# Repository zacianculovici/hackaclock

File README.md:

# hackaclock
My Stardance BLARE alarm clock!!!

## Inspiration
Really, I just saw the BLARE mission and thought it was really cool, but I made the case inspired by one of those old alarm clocks with the angled screens. I also added a cool cutout and some bevelling to make it look nice. 

## Challenges
I ran into some pretty tough issues while doing CAD. I made a dumb decision at the start to use blender for my CAD even though it's not exactly a CAD program. Loads of non-manifold errors and geometry issues (that might just be why my commit history looks terrible). I spent over 13 hours just getting the CAD done! Despite these problems, I am still very happy with the result and the CAD (in my humble opinion) looks great.

## Files
* [Firmware: hackaclock.ino](firmware/hackaclock.ino)
* [Box: Hackaclock-Box.stl](Production/Hackaclock-Box.stl)
* [Lid: Hackaclock-Lid.stl](Production/Hackaclock-Lid.stl)
* [PCB: Board.step](Production/Board.step)
* [Gerbers: fab_files.zip](Production/fab_files.zip)

## Specs
### BOM
* 6x Cherry MX Switches
* 6x Blank Keycaps
* 1x Unimportant jumper header
* 1x XIAO ESP32-C3
* 4x M3x16 bolts
* 4x M3 heat-set inserts
* 1x Buzzer

### Firmware
I am using the most barebones firmware to begin, but I will make it super cool after I build. Currently it only gets the local time via WiFi with no fallback, but I will eventually add:
#### Coming soon
* Alarms
* Manual time setting
* Timer/stopwatch
* Alarm snooze
* Buzzer goes beeeeeeep
* More features...

### CAD
The CAD is a very simple (13h worth of simple) box and lid with a slot for the display and supports for the PCB.

## PCB:
Here is the Schematic and PCB layout for hackaclock.

---
<sup><sub>2026 - Zac Ianculovici | [Contact](mailto:zachary.ianculovici@gmail.com) | [Slack](https://hackclub.enterprise.slack.com/team/U0BMLT1CFB3) | [Stardance](https://stardance.hackclub.com/@zac_i)</sub></sup>

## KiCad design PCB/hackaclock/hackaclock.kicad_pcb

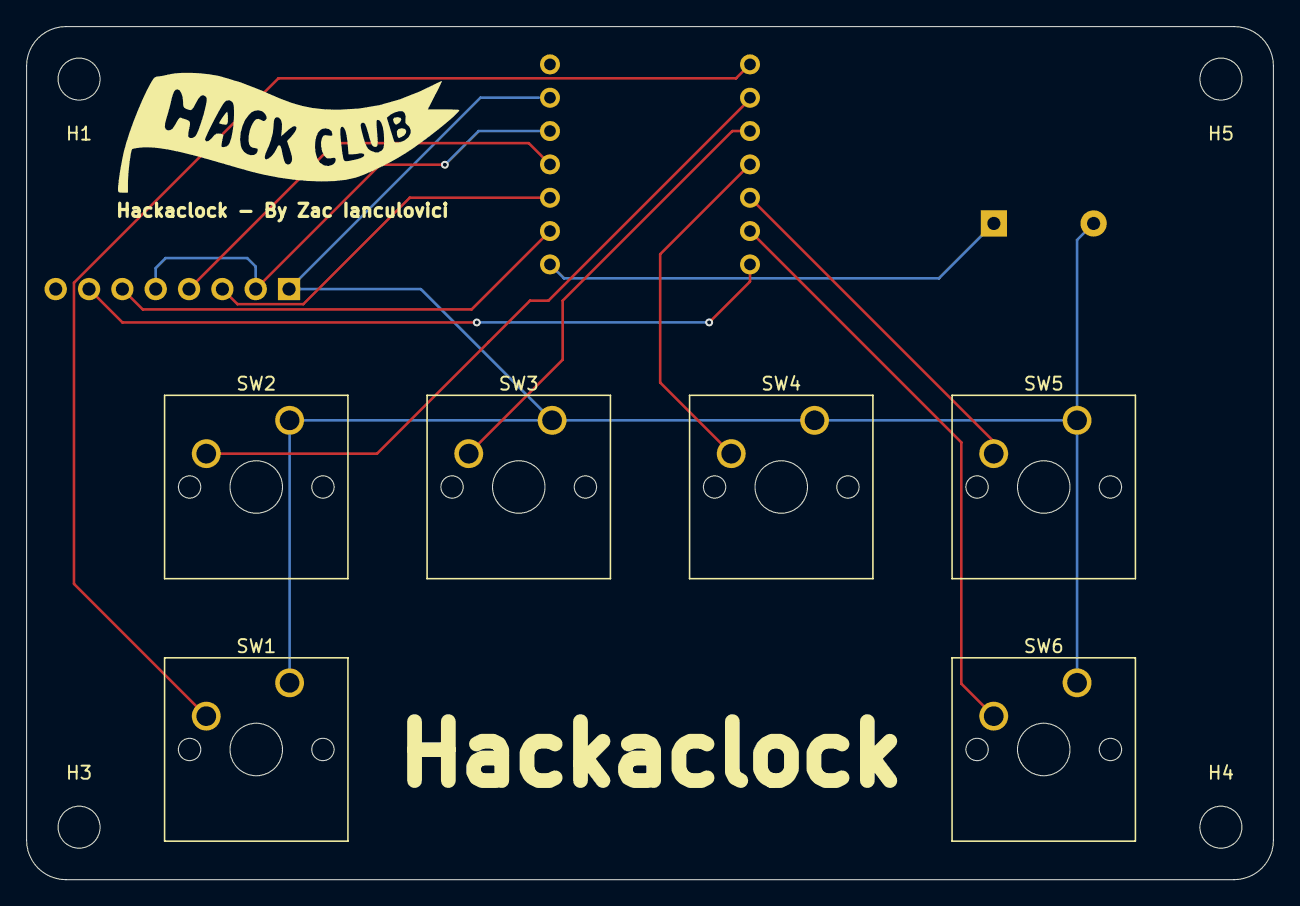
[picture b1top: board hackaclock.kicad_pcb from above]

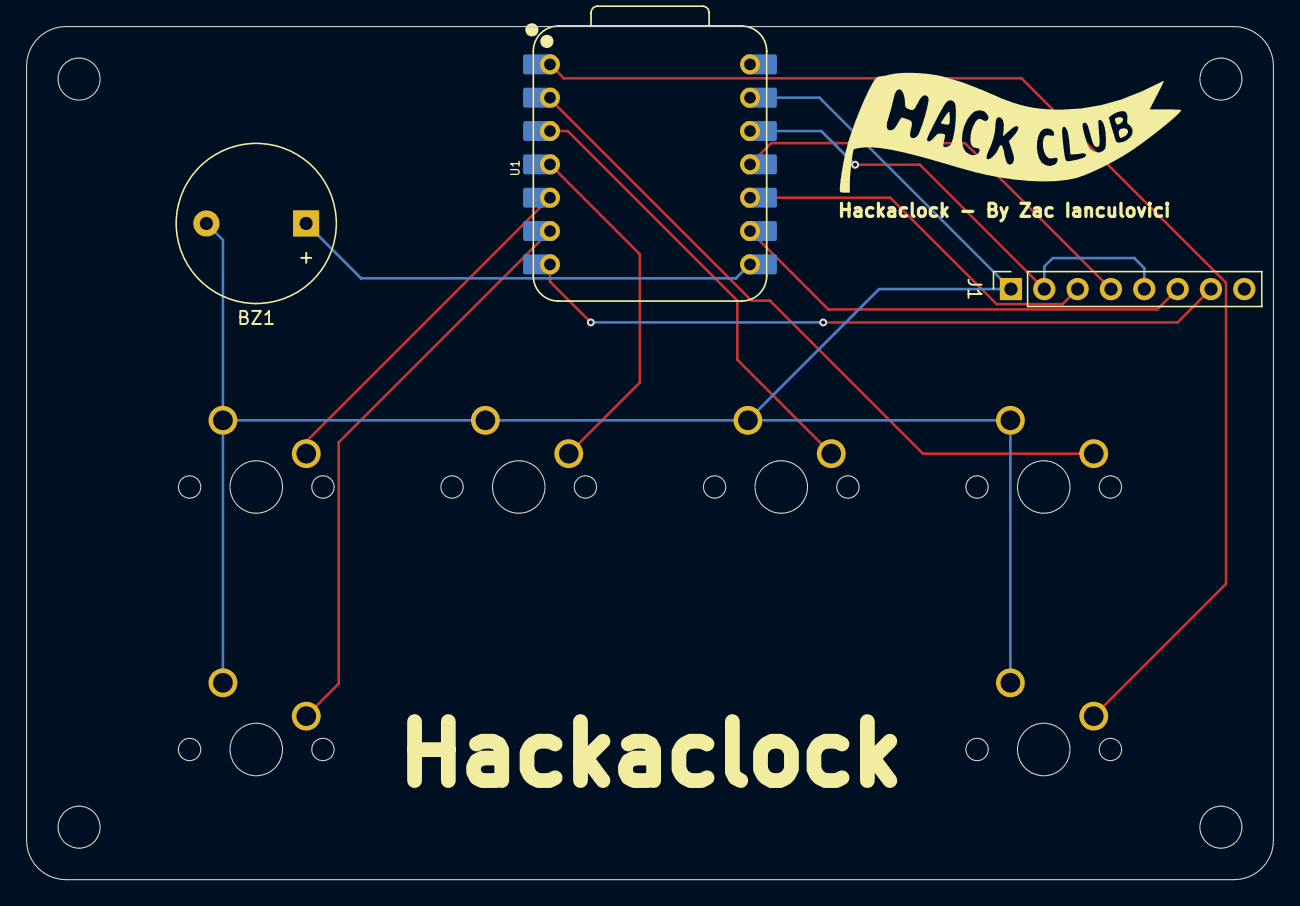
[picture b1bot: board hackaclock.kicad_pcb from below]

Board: 2 copper layers, 95.0 x 65.0 mm, 15 parts (4 on the bottom side), 13 nets.

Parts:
BZ1: Buzzer; Buzzer_12x9.5RM7.6
H1, H3, H4, H5: MountingHole; MountingHole_3.2mm_M3
Hackaclock - By Zac Ianculovici: LOGO
Hackaclock - By Zac Ianculovici#2: LOGO
J1: Conn_01x08_Pin; PinSocket_1x08_P2.54mm_Vertical
SW1, SW2, SW3, SW4, SW5, SW6: SW_Push; SW_Cherry_MX_1.00u_PCB
U1: XIAO-ESP32-C3-SMD; XIAO-ESP32-C3-DIP

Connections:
+3V3: J1.2, J1.5, U1.12 (3V3_OUT)
/CS: J1.7, U1.7 (D6)
/DC: J1.6, U1.9 (D8)
/SCL: J1.3, U1.10 (D9/BOOT)
/SDA: J1.4, U1.11 (D10)
GND: BZ1.2 (-), J1.1, J1.8, SW1.1, SW2.1, SW3.1, SW4.1, SW5.1, SW6.1, U1.13 (GND)
unnamed: BZ1.1 (+), U1.8 (D7)
unnamed: SW1.2, U1.1 (D0)
unnamed: SW2.2, U1.2 (D1)
unnamed: SW3.2, U1.3 (D2)
unnamed: SW4.2, U1.4 (D3)
unnamed: SW5.2, U1.5 (D4)
unnamed: SW6.2, U1.6 (D5)
